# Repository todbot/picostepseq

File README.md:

# PicoStepSeq

PicoStepSeq is an 8-step MIDI sequencer using a Raspberry Pi Pico, an I2C SSD1306 OLED display, a rotary encoder. and 8 "Step Switches".  It outputs via USB MIDI and Serial MIDI via TRS-A 3.5mm.

It is designed as a potential DIY kit for people with beginner-level soldering skills
Part count is minimal, with all parts are through-hole, except for the two MIDI jacks,
which are easily solderable by hand.

## Demo videos

https://user-images.githubusercontent.com/274093/185005269-afb4c3f7-0ca1-40c8-a17d-6e4756943d87.mov

https://user-images.githubusercontent.com/274093/196536711-abd25514-53b9-4710-8ff6-1fa3559f0028.mp4

Also featured in [MagPi Magazine #123](https://magpi.raspberrypi.com/articles/picostepseq-rp2040-music-maker), and [in print too](https://magpi.raspberrypi.com/issues/123)!

## How to use

In use, PicoStepSeq has two states: Play and Pause.
It is designed so you never have to stop playing to edit and save/load a sequence.
It has 8 sequence slots that can be edited and are persistently saved to flash.

While Playing, the actions are:

- **Pause** -- Tap encoder button
- **Transpose sequence up/down** -- Turn encoder knob
- **Change tempo BPM** -- Push + turn encoder knob
- **Mute / Unmute steps** -- Tap corresponding step key
- **Change step's pitch** -- Hold step key, turn encoder knob
- **Change step's gate** -- Hold step key, push + turn encoder knob
- **Load sequence** -- Push encoder, tap step key 1-8, release encoder
- **Save sequence** -- Push encoder, hold step key 1-8 for 2 secs, release encoder

When Paused, the actions are:
- **Play** -- Tap encoder button
- **Play notes** -- tap corresponding step key to play its pitch
- **Change step's pitch** -- Hold step key, turn encoder knob

Sequence Save & Load:
- On startup, `saved_sequences.json` is read from disk and loaded into the 8 sequence slots
- Upon transitioning from Play to Pause, all 8 sequences will be written to disk as `saved_sequences.json`

### Step Keys

The 8 "step keys" have an LED that indicate current mute/unmute status and which step is currently being played.
Tap on a step key to mute/unmute it. Hold a key and turn the encoder knob to change the pitch of that step.

### Rotary Encoder

Turning the encoder adjusts the transpose amount of the playing sequence.  Push + turning adjusts the tempo.

### Display

PicoStepSeq can be used without really looking at the display (which is good because the display is very small).
The display is hopefully clear. It's divided into the top section showing 8 notes with gate info and the bottom section showing which sequence, current BPM & transpose, and if the sequencer is in play/pause mode.

### MIDI

PicoStepSeq outputs both USB MIDI and Serial MIDI.

There is preliminary support for syncing to MIDI Clock.

## Building

The schematic and PCB design is in the `hardware` directory.

An [OSHPark project](https://oshpark.com/shared_projects/vPWjBrmO) of the PCBs is ready to go.

[Build guide to come!]

### Enclosure

A 3d-printable enclosure is [available on Printables](https://www.printables.com/model/260860-picostepseq-midi-step-sequencer-w-raspberry-pi-pic)

The current enclosure is designed for the case where sockets are used for both the Pico and the OLED display.
This is so either can be removed for other uses, so you don't have to sacrifice a Pico if you want to try this out.

### Installing Firmware (CircuitPython)

#### Arduino version:

Probalby the easiest way to get PicoStepSeq running is to install the precompiled Arduino UF2
version in the [Releases](https://github.com/todbot/picostepseq/releases) section.

The Arduino firmware lives in `arduino/picostepseq`.
To compile the Arduino firmware, see the top of the `picostepseq.ino` file.

#### CircuitPython version:

To install the CircuitPython version:

The firmware lives in the `circuitpython/picostepseq` directory.

1. Copy all files in the `circuitpython/picostepseq` directory to the CIRCUITPY disk.

   If using a Mac terminal, you can do:
   ```sh
   cd picostepseq/circuitpython/picostepseq
   cp -rX * /Volumes/CIRCUITPY
   ```

2. Install the CircuitPython libraries `adafruit_displayio_ssd1306` and `adafruit_display_text`

   You can use the `circup` tool in Terminal for this:

   ```sh
   circup install adafruit_displayio_ssd1306 adafruit_display_text
   ```

   If you do not have `circup`, then you will need to copy the following files/dirs from the
   [Adafruit_CircuitPython_Bundle 8.x](https://circuitpython.org/libraries):
   ```
   adafruit_bitmap_font/
   adafruit_display_text/
   adafruit_displayio_ssd1306.mpy
   ```

3. Reset the board and the sequencer should come up!

   (The reset is important so that `boot.py` is run, which allows you to save sequences)

### Installing the Firmware (Arduino)

The Arduino version is a bit more tricky to get going. See the top of the `picostepseq.ino` file for details.

## Bill of Materials

Here is a [Digikey cart with most parts](https://www.digikey.com/short/8qh7p87z).

Links also included below for major parts

For basic USB MIDI functionality:

- 1 - "picostepseq" PCB ([OSHpark](https://oshpark.com/shared_projects/vPWjBrmO), also see "hardware" directory for gerbers)
- 1 - Raspberry Pi Pico ([Adafruit](https://www.adafruit.com/product/4864), [Digikey](https://www.digikey.com/en/products/detail/raspberry-pi/SC0915/13624793))
- 1 - 0.96" I2C OLED SSD1306 128x64 display ([Amazon](https://amzn.to/3K1ZAoo))
  - w/ pins in order GND, VCC, SCL, SDA; some have GND & VCC swapped
- 1 - EC11 style rotary encoder w/ switch ([Digikey](https://www.digikey.com/en/products/detail/bourns-inc/PEC11R-4215F-S0024/4499665), [Adafruit](https://www.adafruit.com/product/377)]
- 8 - "step switch" w/ built-in LED ([Adafruit](https://www.adafruit.com/product/5519)]
- 8 - resistor 1k (R1-R8, 500 ohm also works) ([Digikey](https://www.digikey.com/en/products/detail/stackpole-electronics-inc/CF18JT1K00/1741612), [Adafruit](https://www.adafruit.com/product/4294)]
- 1 - encoder knob ("Davies 1900" style works well, [Adafruit](https://www.adafruit.com/product/5541))

For both USB + Serial MIDI, add:

- 2 - 3.5mm TRS jack, SJ-3523-SMT-TR (J1,J2)
([Digikey](https://www.digikey.com/en/products/detail/cui-devices/SJ-3523-SMT-TR/281297))
- 1 - 6N138 optoisolator (U2) ([Digikey](https://www.digikey.com/en/products/detail/liteon/6N138/1969179))
- 1 - 100n capacitor (C1) ([Digikey](https://www.digikey.com/en/products/detail/vishay-beyschlag-draloric-bc-components/K104K15X7RF5TL2/286538), [Adafruit](https://www.adafruit.com/product/753))
- 1 - resistor 10 ohm (R1)
- 1 - resistor 30 ohm (R2) (47 ohm also works)
- 1 - resistor 220 ohm (R3)
- 1 - resistor 4.7k ohm (R4)

And if you've not used ["TRS MIDI"](https://minimidi.world/#types) and have normal 5-pin DIN MIDI jacks
on your gear, you'll need a few:
- Type A" MIDI adapter ([PerfectCircuit](https://www.perfectcircuit.com/make-noise-0-coast-midi-cable.html) or [Amazon](https://amzn.to/3Tb6DiU))

You can attach the Pico & the OLED display how you like, but if using the 3d-printable "picostepseq_headers" case, you will also need:

- 2 - 20-pin header socket ([Digikey](https://www.digikey.com/en/products/detail/sullins-connector-solutions/PPPC201LFBN-RC/810192), [Adafruit](https://www.adafruit.com/product/5583))
- 2 - 20-pin header pins ([Digikey](https://www.digikey.com/en/products/detail/adam-tech/PH1-20-UA/9830398), [Adafruit ](https://www.adafruit.com/product/392))
- 1 - 4-pin female (same as above, break off 4-pin chunk)

## Firmware Design (CircuitPython)

Timing in CircuitPython is all over the place and there's no periodic timer support (like `Timer` in MicroPython).
So, in order to minimize timing jitter due to I2C `displayio` transactions, the UI & display update code
is designed so only the minimal amount of information is changed on the display in one iteration of the main
UI loop. This is most noticable when loading a new sequence: the entire sequence is revealed only after a full
loop.

The sequencer "beat scheduler" also tries to account for the variation in CircuitPython timing by
measuring an "error" on the delta_t between beats and applies that to the next beat

[More to come!]

Thanks to [Winterbloom](https://github.com/wntrblm) and [@theacodes](https://github.com/theacodes) for the awesome
[SmolMIDI library](https://github.com/wntrblm/Winterbloom_SmolMIDI) for efficient MIDI parsing.
(and for [really cool Eurorack synthesizer devices](https://winterbloom.com/shop))

**Note:** If you have an [Adafruit MacroPad RP2040](https://www.adafruit.com/product/5128),
you can experiment with the sequencer without building any hardware! The code will auto-detect
if it's running on a MacroPad. Rotate the MacroPad so the display is on the left,
then the sequencer keys are arranged as two rows of four.

Here's a demo video of an early dev version of the sequencer running on the MacroPad:

https://user-images.githubusercontent.com/274093/196534059-c9460560-1983-42a2-818f-853e90acd9bf.mp4

## PCB layout

This is the original version that has a typo on the MIDI jacks.

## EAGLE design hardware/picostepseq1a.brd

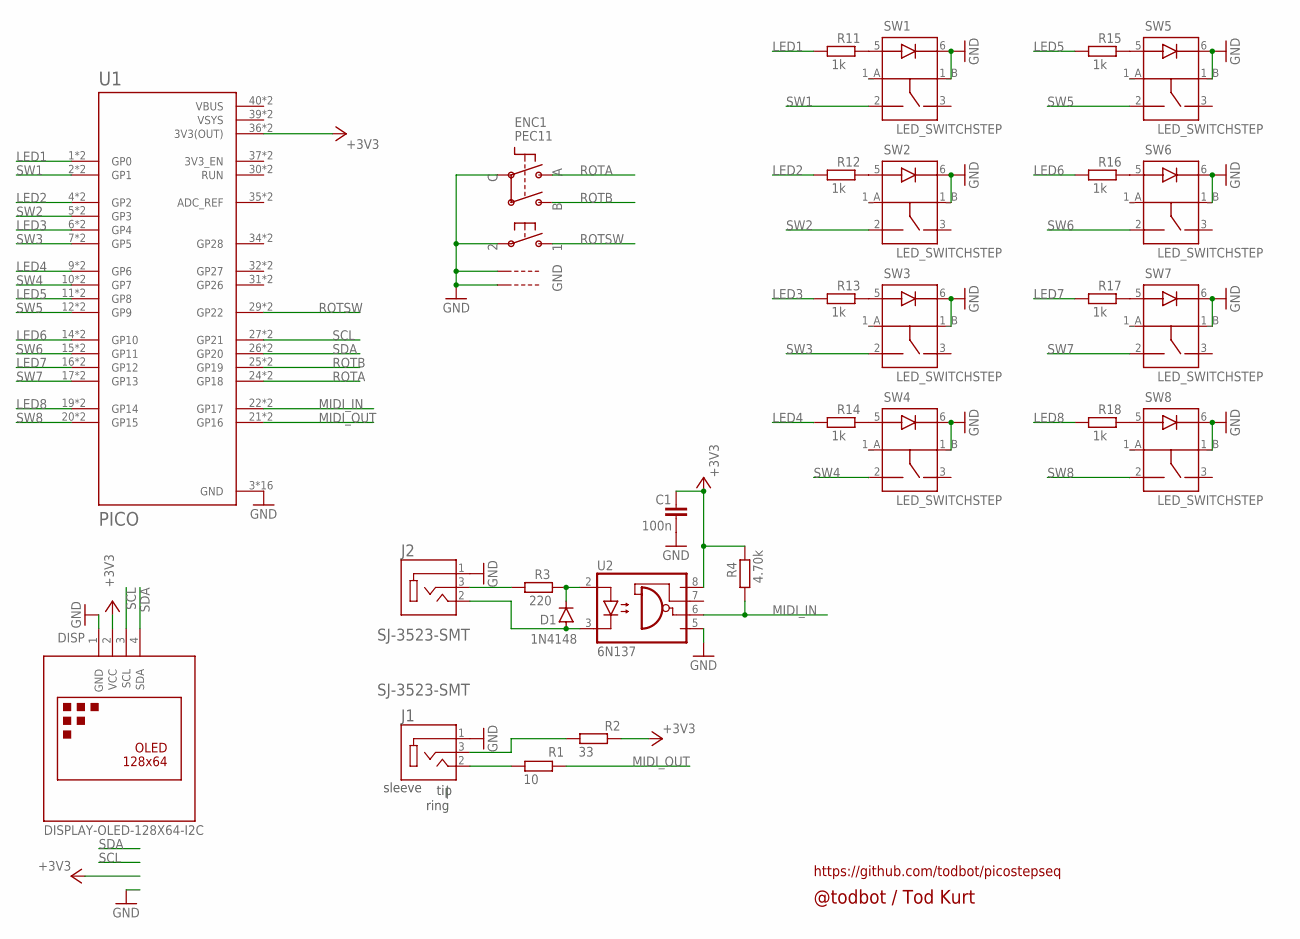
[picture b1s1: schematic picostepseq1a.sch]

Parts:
C1: 100n; C025-025X050
D1: 1N4148; DO35-7
DISP: DISPLAY-OLED-128X64-I2C
ENC1: PEC11; PEC11+SWITCH
J1, J2: SJ-3523-SMT; CUI_SJ-3523-SMT
R1: 10; 0204/7
R2: 33; 0204/7
R3: 220; 0204/7
R4: 4.70k; 0204/7
R11, R12, R13, R14, R15, R16, R17, R18: 1k; 0204/7
SW1, SW2, SW3, SW4, SW5, SW6, SW7, SW8: LED_SWITCHSTEP; LED_SWITCH_STEP
U1: PICO; PICO-PKG-NO_DEBUG
U2: 6N137; DIL08

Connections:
+3V3: C1.1, DISP.2 (VCC), R2.2, R4.1, U1.36 (3V3(OUT)), U1.P$36 (3V3(OUT)), U2.8 (VCC)
GND: C1.2, DISP.1 (GND), ENC1.P$2, ENC1.P$C, ENC1.P$GND1, ENC1.P$GND2, J1.1, J2.1, SW1.1_B, SW1.6, SW2.1_B, SW2.6, SW3.1_B, SW3.6, SW4.1_B, SW4.6, SW5.1_B, SW5.6, SW6.1_B, SW6.6, SW7.1_B, SW7.6, SW8.1_B, SW8.6, U1.3 (GND), U1.8 (GND), U1.13 (GND), U1.18 (GND), U1.23 (GND), U1.28 (GND), U1.33 (GND), U1.38 (GND), U1.P$3 (GND), U1.P$8 (GND), U1.P$13 (GND), U1.P$18 (GND), U1.P$23 (GND), U1.P$28 (GND), U1.P$33 (GND), U1.P$38 (GND), U2.5 (GND)
LED1: R11.2, U1.1 (GP0), U1.P$1 (GP0)
LED2: R12.2, U1.4 (GP2), U1.P$4 (GP2)
LED3: R13.2, U1.6 (GP4), U1.P$6 (GP4)
LED4: R14.2, U1.9 (GP6), U1.P$9 (GP6)
LED5: R15.2, U1.11 (GP8), U1.P$11 (GP8)
LED6: R16.2, U1.14 (GP10), U1.P$14 (GP10)
LED7: R17.2, U1.16 (GP12), U1.P$16 (GP12)
LED8: R18.2, U1.19 (GP14), U1.P$19 (GP14)
MIDI_IN: R4.2, U1.22 (GP17), U1.P$22 (GP17), U2.6 (VO)
MIDI_OUT: R1.2, U1.21 (GP16), U1.P$21 (GP16)
unnamed: J1.2, R1.1
unnamed: D1.C, R3.1, U2.2 (A)
unnamed: D1.A, J2.2, U2.3 (C)
unnamed: R11.1, SW1.5
unnamed: R12.1, SW2.5
unnamed: R13.1, SW3.5
unnamed: R14.1, SW4.5
unnamed: R15.1, SW5.5
unnamed: R16.1, SW6.5
unnamed: R17.1, SW7.5
unnamed: R18.1, SW8.5
unnamed: J1.3, R2.1
unnamed: J2.3, R3.2
ROTA: ENC1.P$A, U1.24 (GP18), U1.P$24 (GP18)
ROTB: ENC1.P$B, U1.25 (GP19), U1.P$25 (GP19)
ROTSW: ENC1.P$1, U1.29 (GP22), U1.P$29 (GP22)
SCL: DISP.3 (SCL), U1.27 (GP21), U1.P$27 (GP21)
SDA: DISP.4 (SDA), U1.26 (GP20), U1.P$26 (GP20)
SW1: SW1.2, U1.2 (GP1), U1.P$2 (GP1)
SW2: SW2.2, U1.5 (GP3), U1.P$5 (GP3)
SW3: SW3.2, U1.7 (GP5), U1.P$7 (GP5)
SW4: SW4.2, U1.10 (GP7), U1.P$10 (GP7)
SW5: SW5.2, U1.12 (GP9), U1.P$12 (GP9)
SW6: SW6.2, U1.15 (GP11), U1.P$15 (GP11)
SW7: SW7.2, U1.17 (GP13), U1.P$17 (GP13)
SW8: SW8.2, U1.20 (GP15), U1.P$20 (GP15)
VBUS: U1.40 (VBUS), U1.P$40 (VBUS)
VSYS: U1.39 (VSYS), U1.P$39 (VSYS)

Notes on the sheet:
tip
| ring
sleeve
@todbot / Tod Kurt
https://github.com/todbot/picostepseq

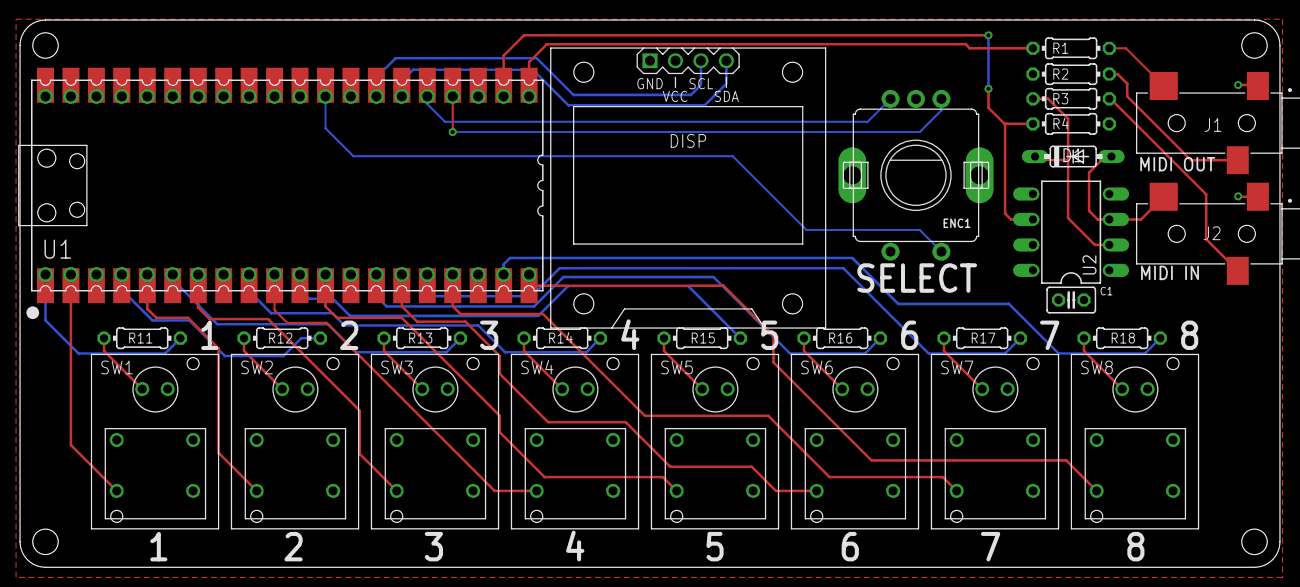
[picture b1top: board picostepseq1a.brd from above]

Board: 2 copper layers, 125.7 x 54.6 mm, 28 parts (0 on the bottom side), 40 nets.

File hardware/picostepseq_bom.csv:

"Qty";"Value";"Device";"Package";"Parts";"Description";"CUI_PURCHASE_URL";"DESCRIPTION";"DIGI-KEY_PART_NUMBER";"MF";"MP";"MPN";"OC_FARNELL";"OC_NEWARK";"PACKAGE";"POPULARITY";"PURCHASE-URL";"SPICEPREFIX";
"1";"";"C-EU025-025X050";"C025-025X050";"C1";"CAPACITOR, European symbol";"";"";"";"";"";"";"";"";"";"65";"";"C";
"1";"";"RASPBERRY_PICO-NO_DEBUG";"PICO-PKG-NO_DEBUG";"U1";"";"";"";"";"";"";"";"";"";"";"";"";"";
"1";"10";"R-EU_0204/7";"0204/7";"R1";"RESISTOR, European symbol";"";"";"";"";"";"";"";"";"";"79";"";"R";
"8";"1k";"R-EU_0204/7";"0204/7";"R11, R12, R13, R14, R15, R16, R17, R18";"RESISTOR, European symbol";"";"";"";"";"";"";"";"";"";"79";"";"R";
"1";"220";"R-EU_0204/7";"0204/7";"R3";"RESISTOR, European symbol";"";"";"";"";"";"";"";"";"";"79";"";"R";
"1";"33";"R-EU_0204/7";"0204/7";"R2";"RESISTOR, European symbol";"";"";"";"";"";"";"";"";"";"79";"";"R";
"1";"4.70k";"R-EU_0204/7";"0204/7";"R4";"RESISTOR, European symbol";"";"";"";"";"";"";"";"";"";"79";"";"R";
"1";"6N137";"6N137";"DIL08";"U2";"MOTOROLA OPTO COUPLER";"";"";"";"";"";"6N137";"1328376";"52M1895";"";"2";"";"";
"1";"DISPLAY-OLED-128X64-I2C";"DISPLAY-OLED-128X64-I2C";"DISPLAY-OLED-128X64-I2C";"DISP";"128x64 Dot Matrix OLED Module based on SSD1306 chip";"";"";"";"";"";"";"";"";"";"";"";"";
"8";"LED_SWITCHSTEP";"LED_SWITCHSTEP";"LED_SWITCH_STEP";"SW1, SW2, SW3, SW4, SW5, SW6, SW7, SW8";"Step switch with LED, like on old drum machines";"";"";"";"";"";"";"";"";"";"";"";"";
"1";"PEC11";"ENCODER_PLUS_SWITCH_BOURNS_PEC11";"PEC11+SWITCH";"ENC1";"Rotary Encoder with Built-In Switch";"";"";"";"";"";"";"";"";"";"";"";"";
"2";"SJ-3523-SMT";"SJ-3523-SMT";"CUI_SJ-3523-SMT";"J1, J2";"Audio Jack Connector 3.5 mm Low Profile Surface Mount Stereo Jack, 3 Pin Right-Angle";"https://www.cuidevices.com/product/interconnect/connectors/a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";"3.5 mm, Stereo, Right Angle, Surface Mount (SMT), 3 Conductors, 0~1 Internal Switches, Audio Jack Connector";"CP-3523SJCT-ND";"CUI Devices";"SJ-3523-SMT-TR";"";"";"";"None";"";"https://pricing.snapeda.com/search/part/SJ-3523-SMT-TR/?ref=eda";"";

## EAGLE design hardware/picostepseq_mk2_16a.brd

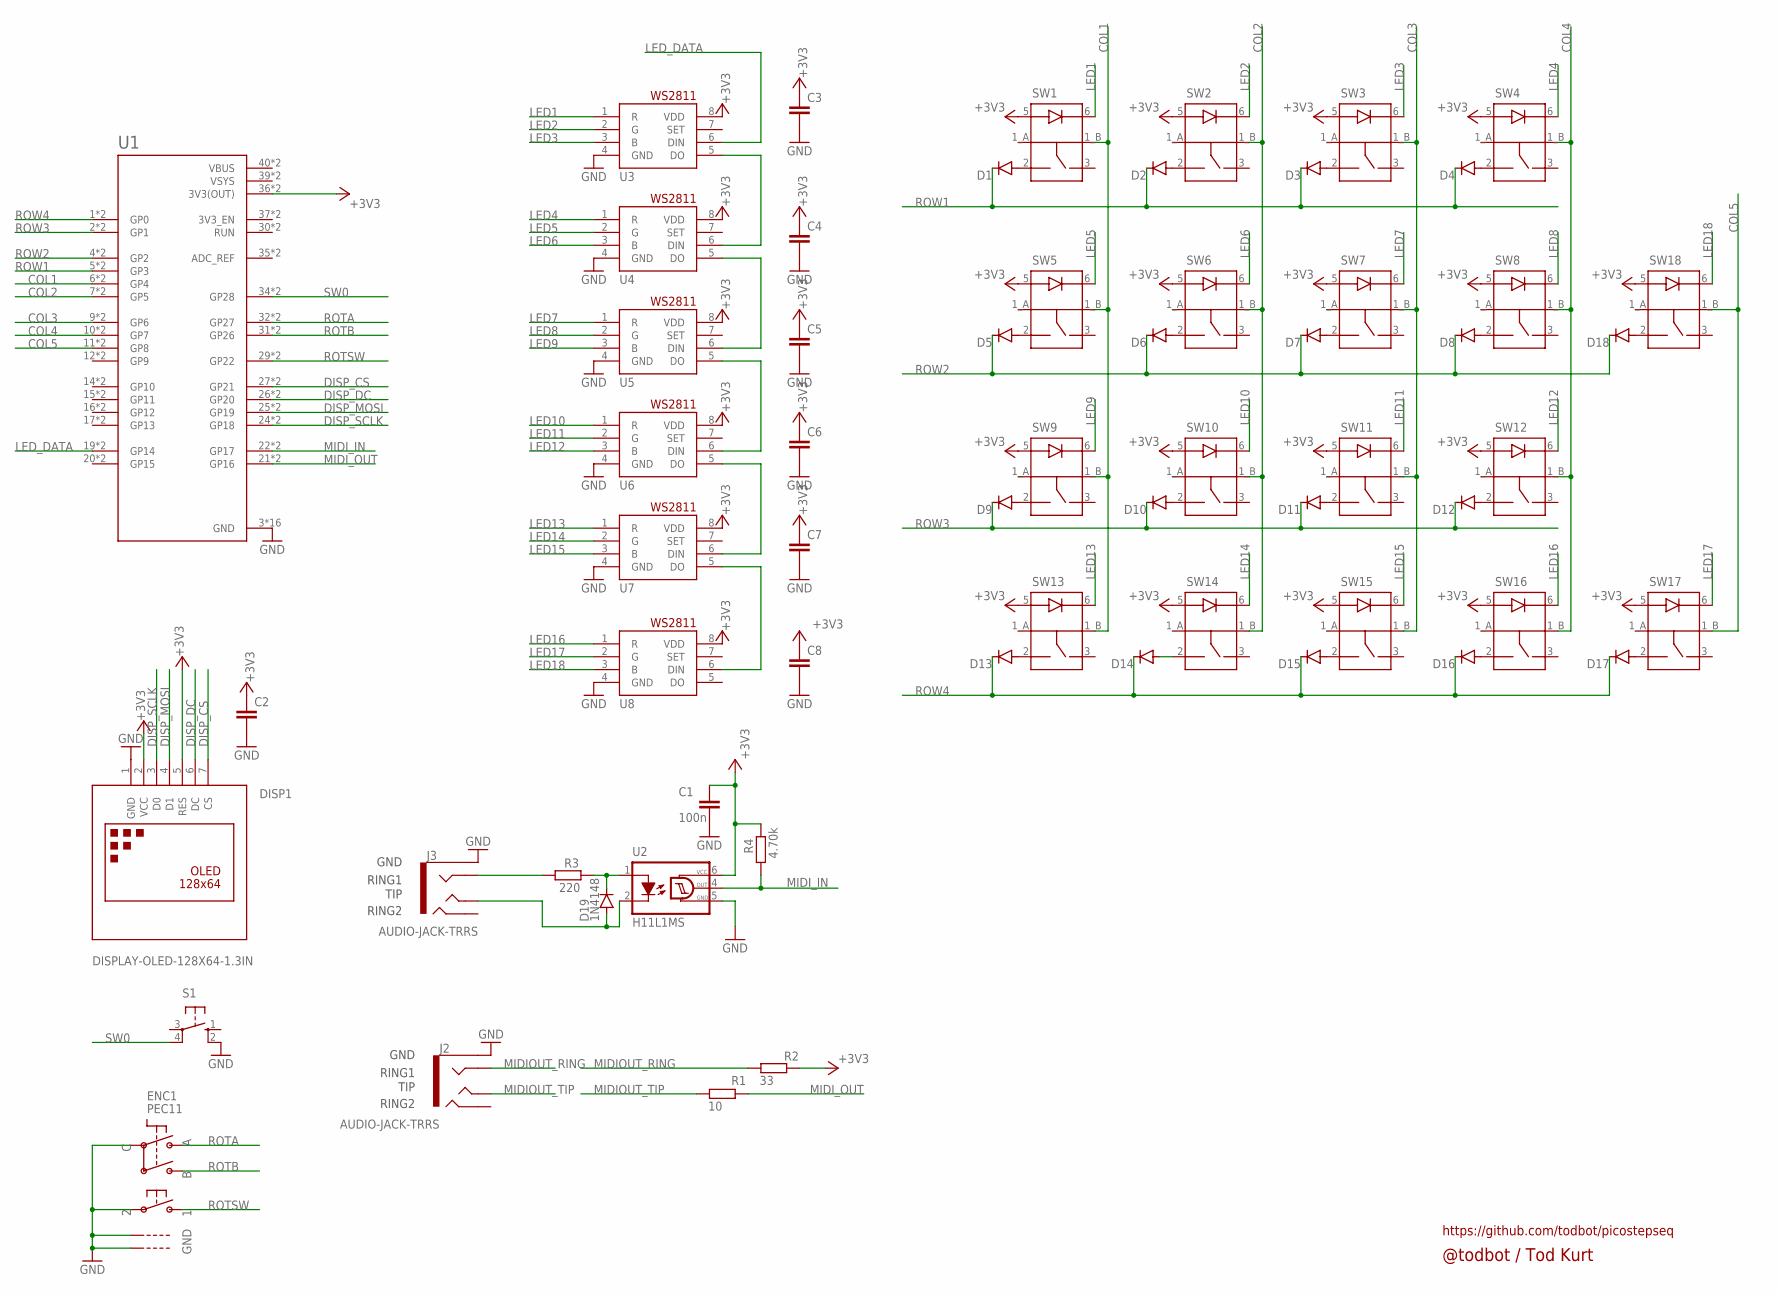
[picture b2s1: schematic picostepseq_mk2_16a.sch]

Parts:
C1: 100n; C0805
C2, C3, C4, C5, C6, C7, C8: C-EUC0805; C0805
D1, D2, D3, D4, D5, D6, D7, D8, D9, D10, D11, D12, D13, D14, D15, D16, D17, D18: DIODE-SOD123; SOD123
D19: 1N4148; SOD123
DISP1: DISPLAY-OLED-128X64-1.3IN
ENC1: PEC11; PEC11+SWITCH
J2, J3: AUDIO-JACK-TRRS; PJ-320D_SPARKFUN
R1: 10; R0805
R2: 33; R0805
R3: 220; R0805
R4: 4.70k; R0805
S1: 10-XX; B3F-10XX
SW1, SW2, SW3, SW4, SW5, SW6, SW7, SW8, SW9, SW10, SW11, SW12, SW13, SW14, SW15, SW16, SW17, SW18: LED_SWITCHSTEP; LED_SWITCH_STEP
U1: RASPBERRY_PICO-NO_DEBUG; PICO-PKG-NO_DEBUG
U2: H11L1MS; DIL6-SMD; MPN2 H11L1S; LCSC C78589
U3, U4, U5, U6, U7, U8: WS2811-SOP8; SO08-SKINNYPADS

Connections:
+3V3: C1.1, C2.1, C3.1, C4.1, C5.1, C6.1, C7.1, C8.1, DISP1.2 (VCC), DISP1.5 (RES), R2.2, R4.1, SW1.5, SW2.5, SW3.5, SW4.5, SW5.5, SW6.5, SW7.5, SW8.5, SW9.5, SW10.5, SW11.5, SW12.5, SW13.5, SW14.5, SW15.5, SW16.5, SW17.5, SW18.5, U1.36 (3V3(OUT)), U1.P$36 (3V3(OUT)), U2.6 (VCC), U3.8 (VDD), U4.8 (VDD), U5.8 (VDD), U6.8 (VDD), U7.8 (VDD), U8.8 (VDD)
COL1: SW1.1_B, SW5.1_B, SW9.1_B, SW13.1_B, U1.6 (GP4), U1.P$6 (GP4)
COL2: SW2.1_B, SW6.1_B, SW10.1_B, SW14.1_B, U1.7 (GP5), U1.P$7 (GP5)
COL3: SW3.1_B, SW7.1_B, SW11.1_B, SW15.1_B, U1.9 (GP6), U1.P$9 (GP6)
COL4: SW4.1_B, SW8.1_B, SW12.1_B, SW16.1_B, U1.10 (GP7), U1.P$10 (GP7)
COL5: SW17.1_B, SW18.1_B, U1.11 (GP8), U1.P$11 (GP8)
DISP_CS: DISP1.7 (CS), U1.27 (GP21), U1.P$27 (GP21)
DISP_DC: DISP1.6 (DC), U1.26 (GP20), U1.P$26 (GP20)
DISP_MOSI: DISP1.4 (D1), U1.25 (GP19), U1.P$25 (GP19)
DISP_SCLK: DISP1.3 (D0), U1.24 (GP18), U1.P$24 (GP18)
GND: C1.2, C2.2, C3.2, C4.2, C5.2, C6.2, C7.2, C8.2, DISP1.1 (GND), ENC1.P$2, ENC1.P$C, ENC1.P$GND1, ENC1.P$GND2, J2.EARTH, J3.EARTH, S1.2 (S1), U1.3 (GND), U1.8 (GND), U1.13 (GND), U1.18 (GND), U1.23 (GND), U1.28 (GND), U1.33 (GND), U1.38 (GND), U1.P$3 (GND), U1.P$8 (GND), U1.P$13 (GND), U1.P$18 (GND), U1.P$23 (GND), U1.P$28 (GND), U1.P$33 (GND), U1.P$38 (GND), U2.5 (GND), U3.4 (GND), U4.4 (GND), U5.4 (GND), U6.4 (GND), U7.4 (GND), U8.4 (GND)
LED1: SW1.6, U3.1 (R)
LED2: SW2.6, U3.2 (G)
LED3: SW3.6, U3.3 (B)
LED4: SW4.6, U4.1 (R)
LED5: SW5.6, U4.2 (G)
LED6: SW6.6, U4.3 (B)
LED7: SW7.6, U5.1 (R)
LED8: SW8.6, U5.2 (G)
LED9: SW9.6, U5.3 (B)
LED10: SW10.6, U6.1 (R)
LED11: SW11.6, U6.2 (G)
LED12: SW12.6, U6.3 (B)
LED13: SW13.6, U7.1 (R)
LED14: SW14.6, U7.2 (G)
LED15: SW15.6, U7.3 (B)
LED16: SW16.6, U8.1 (R)
LED17: SW17.6, U8.2 (G)
LED18: SW18.6, U8.3 (B)
LED_DATA: U1.19 (GP14), U1.P$19 (GP14), U3.6 (DIN)
MIDIOUT_RING: J2.RING1, R2.1
MIDIOUT_TIP: J2.TIP, R1.1
MIDI_IN: R4.2, U1.22 (GP17), U1.P$22 (GP17), U2.4 (OUT)
MIDI_OUT: R1.2, U1.21 (GP16), U1.P$21 (GP16)
unnamed: D18.A, SW18.2
unnamed: D17.A, SW17.2
unnamed: D1.A, SW1.2
unnamed: D2.A, SW2.2
unnamed: D3.A, SW3.2
unnamed: D4.A, SW4.2
unnamed: D5.A, SW5.2
unnamed: D9.A, SW9.2
unnamed: D10.A, SW10.2
unnamed: D11.A, SW11.2
unnamed: D12.A, SW12.2
unnamed: D13.A, SW13.2
unnamed: D14.A, SW14.2
unnamed: D15.A, SW15.2
unnamed: D16.A, SW16.2
unnamed: D6.A, SW6.2
unnamed: U3.5 (DO), U4.6 (DIN)
unnamed: U4.5 (DO), U5.6 (DIN)
unnamed: D7.A, SW7.2
unnamed: U5.5 (DO), U6.6 (DIN)
unnamed: U6.5 (DO), U7.6 (DIN)
unnamed: U7.5 (DO), U8.6 (DIN)
unnamed: D8.A, SW8.2
unnamed: D19.C, R3.1, U2.1 (A)
unnamed: D19.A, J3.TIP, U2.2 (C)
unnamed: J3.RING1, R3.2
ROTA: ENC1.P$A, U1.32 (GP27), U1.P$32 (GP27)
ROTB: ENC1.P$B, U1.31 (GP26), U1.P$31 (GP26)
ROTSW: ENC1.P$1, U1.29 (GP22), U1.P$29 (GP22)
ROW1: D1.C, D2.C, D3.C, D4.C, U1.5 (GP3), U1.P$5 (GP3)
ROW2: D5.C, D6.C, D7.C, D8.C, D18.C, U1.4 (GP2), U1.P$4 (GP2)
ROW3: D9.C, D10.C, D11.C, D12.C, U1.2 (GP1), U1.P$2 (GP1)
ROW4: D13.C, D14.C, D15.C, D16.C, D17.C, U1.1 (GP0), U1.P$1 (GP0)
SW0: S1.4 (P1), U1.34 (GP28), U1.P$34 (GP28)
VBUS: U1.40 (VBUS), U1.P$40 (VBUS)
VSYS: U1.39 (VSYS), U1.P$39 (VSYS)

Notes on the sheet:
@todbot / Tod Kurt
https://github.com/todbot/picostepseq
RING2
RING1
GND
TIP

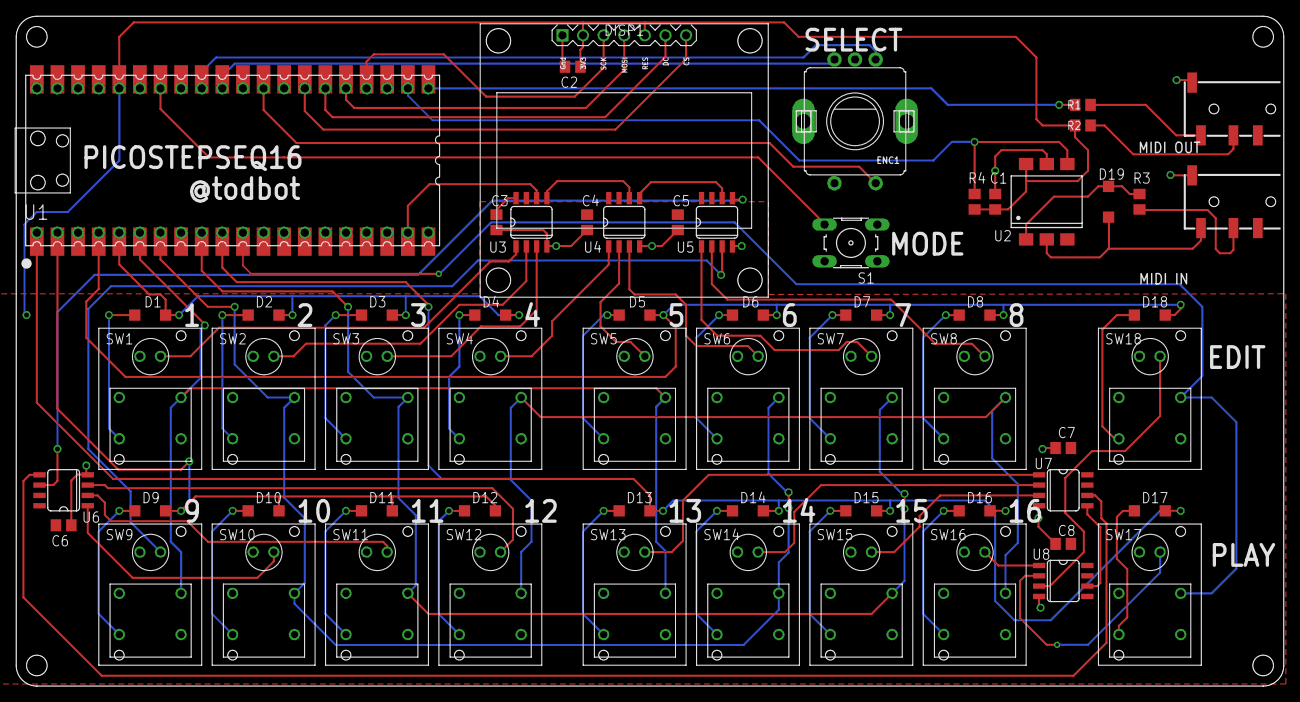
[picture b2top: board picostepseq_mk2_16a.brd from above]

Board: 2 copper layers, 156.2 x 82.5 mm, 62 parts (0 on the bottom side), 70 nets.

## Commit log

2022-08-05 first
2022-08-06 sigh trs-a/b will kill me
2022-08-06 update to knob
2022-08-06 added basic hardware POC test code
2022-08-06 small fixes, submit to fab
2022-08-08 test code on macropad
2022-08-08 macropadrp2040 test working
2022-08-08 macropadrp2040 test: UI is getting closer
2022-08-09 okay time to try Step objects
2022-08-09 redesign LED update method, encoder knob push hold to stop finally works
2022-08-09 gate bars installed
2022-08-09 changed to vertical display layout to better fit macropad
2022-08-09 pulled out displayio UI to own class
2022-08-09 trying out different timing strategies
2022-08-10 oops
2022-08-10 fix play/pause bug, fix mute/unmute bug, fix playing when stopped bug
2022-08-10 move MIDI IN and MIDI OUT labels because I am dumb
2022-08-11 lets try reading/writing sequences to disk as json
2022-08-11 may as well keep this
2022-08-11 add seqno sequence number to display
2022-08-11 seq save/load UI now makes sense
2022-08-11 add horizontal display variant (for real picostepseq)
2022-08-11 add more non REPL verify output
2022-08-12 just throw it all in to git for the moment
2022-08-12 fix lag from big i2c ssd1306 updates
2022-08-12 move hardware to its own object
2022-08-12 cleanup, new font for steps (thx okyeron)
2022-08-12 new more readable screen layout
2022-08-13 added serial midi out
2022-08-14 display: 8 steps in one line now
2022-08-14 new font for notes
2022-08-15 midi beat sync does not work yet
2022-08-16 optimize bpm updates so only number changes
2022-08-16 midi clock sync mostly works now
2022-08-16 cleanup
2022-08-16 some UI docs
2022-08-17 small tweaks
2022-08-17 macropad sorta working again
2022-08-17 remove test files
2022-08-17 bdf to pcf font
2022-08-17 update readme with bom
2022-08-18 update stl, update gerbers
2022-08-18 small bugfix
2022-08-18 update readme with smolmidi shoutout
2022-08-18 add arduino test
2022-08-18 add spacer for oled
2022-08-18 fix arduino hardware test display
2022-08-19 clarify
2022-08-19 arduino test, added font
2022-08-19 slight circuitpython reorg
2022-08-19 arduino test: use a debouncer
2022-08-20 add oshpark link
2022-08-21 arduino: basic UI functionality
2022-08-21 add midi out, add gate bars
2022-08-21 arduino version now close to circuitpython version, feature-wise
2022-08-22 small readme update
2022-08-22 remove extranous prints, elapsed time printer, comments
2022-08-22 circuitpython: reduce lag when updating transpose by separating text & value
2022-08-22 arduino: note preview working
2022-08-22 readme note about trs-a midi
2022-08-22 make sequencer noteoct display match midi notes sent
2022-08-22 arduino now has edit/mute display
2022-08-24 added some assembly pics
2022-08-24 rename assembly pics
2022-08-24 add designators until I get the parts table up
2022-08-24 update PCB info about gerbers
2022-08-24 unused code remove
2022-08-25 add taller version of top STL
2022-08-25 added more images
2022-10-13 emillis no more
2022-10-14 commit 16-ch idea
2022-10-18 added macropad demo video to README
2022-11-24 "finish" picostepseq_mk2_16
2023-02-02 added magpi link
2023-02-15 add diode to original picostepseq board, submit fab run
2023-03-10 smd-ish version of picostepseq16
2023-03-30 added picostepseq1a_sch.pdf
2023-04-21 arduino: describe how to actually install arduino version; make more obvious which MIDI channel is sends on; prefill sequence with random (and non-zero velocity) sequence data if "saved_sequences.jso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
2023-04-21 arduino: cleanup, add rudimentary midi clock receive that even mostly works
2023-04-22 arduino: uart midi in clock sync, small display cleanup
2023-04-22 circuitpython: note how to install libraries. fixes #1
2023-04-22 just turning some of the brd layers on
2023-04-22 arduino: match display mutes to CirPy version
2023-04-28 arduino: midiclock out and in
2023-04-28 arduino: try to figure out small lag in midi notes with clockout
2023-04-28 arduino: default sequences generated on first run, no need for data dir any more. midi clock forward (untested)
2023-04-30 arduino: midi forward, and cleanup
2023-04-30 arduino: fix midi forward (OMNI!) and other cleanup, prepping for config screen
2023-05-01 arduino: fix midi in clock tempo calc; add config struct for future use, badly implemented config screen, display pos_t struct
2023-05-02 arduino: still having issues with first notes not turning off when midi in clock
2023-05-02 arduino: fixed first time midi clocked notes
2023-05-02 arduino: sequencer.h retab
2023-05-03 arduino: reworked config screen, works!
2023-05-03 gitignore update
2023-06-19 config fixes
2023-06-19 add midi channel to picostepseq circuitpython
2023-06-19 update readme about arduino verison
2023-08-16 fix macropad
2023-08-16 fix transpose val display for macropad
2025-10-19 update readme and ignore
2025-10-19 update method function for v10 of adafruit lib for macropad

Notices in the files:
parts and their libraries:
diy-modules: Released under the Creative Commons Attribution 4.0 International License: http://creativecommons.org/licenses/by/4.0
